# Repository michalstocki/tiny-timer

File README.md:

# Minutnik na ATtiny13A

Firmware w czystym C (`avr-gcc -Os`, bez Arduino core), instrukcja montażu na płytce stykowej, programowanie przez Arduino UNO, kalibracja i testy odbiorcze. Materiały dla użytkownika są po polsku.

| Co | Gdzie |
| --- | --- |
| Instrukcja montażu (kroki, adresy otworów, rysunki, sprawdzenia) | [docs/instrukcja-montazu.md](docs/instrukcja-montazu.md) |
| Programowanie: ArduinoISP, fuse'y, wgrywanie | [docs/programowanie.md](docs/programowanie.md) |
| Kalibracja czasu (OSCCAL) | [docs/kalibracja.md](docs/kalibracja.md) |
| Testy odbiorcze (tabela do wypełnienia) | [docs/testy-odbiorcze.md](docs/testy-odbiorcze.md) |
| Diagnostyka | [docs/diagnostyka.md](docs/diagnostyka.md) |
| Plan B: ATtiny25/45/85 z ramką i dzwonkiem | [docs/plan-b.md](docs/plan-b.md) |
| Netlista i mapa pinów | [docs/schemat.md](docs/schemat.md) |
| Gotowe pliki `.hex` i raport `avr-size` | `dist/` |
| Źródła firmware i `Makefile` | `firmware/` |
| Generator rysunków/instrukcji i weryfikacja sieci | `tools/breadboard/` |
| Symulacja logiki firmware na komputerze | `tools/sim/` |

## Szybki start

```bash
cd firmware
make                                    # buduje i drukuje rozmiary (avr-gcc z PATH lub z Arduino IDE)
make sig   PORT=/dev/cu.usbmodemXXXX    # Etap 1: sygnatura 0x1e9007 (ATtiny w gnieździe programatora)
make fuses PORT=/dev/cu.usbmodemXXXX    # Etap 2
make flash PROG=test_tone PORT=...      # Etapy 3-5: test_tone, test_display, test_buttons
make flash PROG=timer PORT=...          # Etap 6
```

Weryfikacja bez sprzętu:

```bash
tools/sim/run.sh                                 # logika minutnika (ATtiny13A)
SIM_FLAGS="-DFEATURE_BAR=1 -DFEATURE_BELL=1" tools/sim/run.sh   # plan B
SIM_TARGET=calib tools/sim/run.sh                # program kalibracyjny
cd tools/breadboard && python3 design.py && python3 test_design.py
```

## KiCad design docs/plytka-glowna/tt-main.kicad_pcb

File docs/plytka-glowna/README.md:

# Płytka główna (klin 4): projekt do zamówienia

Dwuwarstwowa płytka **40 × 24 mm** z elementami THT dla obudowy [klin 4](../obudowa-klin-4/README.md). Rozmieszczenie, zarys, otwory M2,5 i wysokości są z [`pcb-klin3`](../pcb-klin3/README.md) i **nie zostały zmienione**, więc model obudowy pozostaje ważny. Nowe jest trasowanie, stopki produkcyjne, opisy i pliki do fabryki.

**Status: Gerbery wyeksportowane i sprawdzone w KiCadzie 10.0.7** (DRC KiCada bez błędów, także z regułą odstępu 0,25 mm; Gerbery obejrzane w GerbView). Do fabryki wysyłasz [`produkcja/tt-main-gerber.zip`](produkcja/tt-main-gerber.zip). Przed zamówieniem zmierz jeszcze wysokość C3 (ryzyko 2).

## Pliki

| Plik | Co to |
| --- | --- |
| [`tt-main.kicad_pcb`](tt-main.kicad_pcb) | projekt dla KiCada (format v7, sprawdzony w KiCadzie 10.0.7): obrys, otwory, stopki, sieci, ścieżki, opisy |
| [`trasowanie.json`](trasowanie.json) | zapisane trasowanie (źródło dla pliku KiCada) |
| [`plytka-strona-elementow.svg`](plytka-strona-elementow.svg), [`plytka-strona-lutowania.svg`](plytka-strona-lutowania.svg) | podglądy obu stron z miedzią i opisami |
| [`plan-montazu.svg`](plan-montazu.svg), [`plan-pomiarow.svg`](plan-pomiarow.svg) | rysunki do instrukcji |
| [`instrukcja-montazu.md`](instrukcja-montazu.md) | montaż krok po kroku z kontrolami |
| [`bom.csv`](bom.csv) | lista części |
| [`produkcja/tt-main-gerber.zip`](produkcja/tt-main-gerber.zip) | **plik do wysłania do fabryki**: 7 warstw Gerber, wiercenia PTH i NPTH (Excellon, mm), plik zadania `.gbrjob` |
| `produkcja/` (reszta) | wynik `export_fab.sh`: rozpakowane Gerbery (`gerber/`), raporty DRC KiCada (`drc-kicad.txt`, `drc-kicad-bledy.txt`), mapy wierceń (`mapa-wiercen/`, poza zipem), podglądy `kicad-F.svg` i `kicad-B.svg` |

## Parametry do zamówienia (typowa fabryka 2-warstwowa, np. JLCPCB lub PCBWay)

| Parametr | Wartość |
| --- | --- |
| Warstwy / materiał | 2, FR-4, 1,6 mm, miedź 1 oz (35 µm) |
| Wymiary | 40 × 24 mm, narożniki R3, tolerancja zarysu ±0,2 mm (obudowa przyjmuje ±0,3) |
| Wykończenie pól | HASL bezołowiowy (do lutowania ręcznego wystarczy; ENIG droższy, bez zalet tutaj) |
| Maska, opis | domyślna zielona maska i biały opis |
| Najmniejsza ścieżka / odstęp | 0,30 / 0,28 mm w projekcie (fabryki dają 0,127 mm, więc duży zapas) |
| Najmniejsze wiercenie | 0,4 mm (przelotka, 1 szt.), pola 0,8…1,2 mm, otwór M2,5: 2,7 mm niemetalizowany |
| Liczba sztuk | najmniejsza oferowana (zwykle 5); wystarczy do próby i zapasu |
| Pozostałe opcje | domyślne; fabryka może dodać numer zamówienia na płytce (w miejscu bez miedzi), na ogół można go wyłączyć za dopłatą |

Nazwy opcji w formularzach fabryk różnią się, ale wszystkie powyższe wartości są standardowe. **Zamów kilka sztuk**: płytka jest mała i tania, a pierwsza wersja zawsze może wymagać poprawki.

## Co sprawdziłem

- **DRC własny** ([`tools/pcb/fab_drc.py`](../../tools/pcb/fab_drc.py)), na dokładnej geometrii: 0 błędów. Najmniejszy odstęp miedzi **0,28 mm** (wymagane 0,25), miedź ≥ 0,5 mm od krawędzi płytki, miedź ≥ 3,0 mm od osi otworów M2,5, pierścienie pól ≥ 0,4 mm, przelotka 0,8/0,4 (pierścień 0,2 mm), odstęp otworów ≥ 1,18 mm. Test ujemny: usunięta ścieżka, ścieżka w polu innej sieci i miedź przy krawędzi są wykrywane.
- **Łączność (LVS):** z geometrii miedzi wyliczona łączność jest zgodna z netlistą: każda z 12 sieci w jednym kawałku, 0 zwarć.
- **Netlista** zgodna z referencją z [`tools/breadboard/design.py`](../../tools/breadboard/design.py) (ta sama, z której powstała instrukcja na płytce stykowej), po pominięciu przycisków, modułu OLED i opcjonalnych R7/R8.
- **Zgodność z obudową:** żaden element nie został przesunięty, obrysy i wysokości są z `board.py`, więc wynik kolizji z [README klina 4](../obudowa-klin-4/README.md) pozostaje ważny. Zmienił się tylko rozstaw nóżek C3 (patrz niżej), w obrysie elementu.

- **KiCad 10.0.7** (`export_fab.sh`): plik wczytuje się bez błędów; DRC KiCada: 0 błędów, 0 niepołączonych pól. Zostały same dopuszczalne ostrzeżenia: 18 × brak biblioteki `TT` (stopki są wbudowane w plik), 32 × obrys elementu na polu (maska go przytnie), 4 × stykające się obrysy C2 i C3. Dodatkowo DRC z ostrzejszymi regułami (odstęp 0,25 mm, miedź–krawędź 0,5 mm, otwór–otwór 0,5 mm): 0 błędów; test ujemny z odstępem 0,29 mm wskazuje dwa miejsca z 0,28 mm przy U1.5, czyli KiCad liczy to samo co własny DRC.
- **Napisy w miedzi** (na prośbę fabryki, do kontroli, że warstwy nie są zamienione ani odbite): „TOP” na F.Cu w prawym górnym rogu strony elementów i „BOT” na B.Cu nad napisem TT-MAIN, lustrzany, więc czyta się od strony lutowania. Wysokość 1,2 mm, kreska 0,25 mm, bez sieci. Miejsce wybiera [`fab_cutext.py`](../../tools/pcb/fab_cutext.py): największy odstęp od miedzi, poza opisami i strefami otworów M2,5. DRC KiCada nie zgłasza ich nawet przy odstępie 0,4 mm; na renderze obu stron czytają się prosto.
- **Gerbery** obejrzane w GerbView (wszystkie warstwy razem) i sprawdzone w plikach: obrys 40 × 24 mm z R3, 43 pola, 1 przelotka i napis (TOP/BOT) na obu warstwach miedzi, 45 otworów w masce na każdej stronie (43 pola + 2 otwory M2,5; przelotka pod maską), opis B odbity poprawnie, wiercenia PTH Ø0,4 (przelotka), Ø0,8, Ø0,9, Ø1,2 i osobny plik NPTH z 2 × Ø2,7.
- **Poprawka po pierwszym eksporcie:** napis „TT-MAIN v1.0” wychodził 0,4 mm poza narożnik płytki, bo generator opisów zakładał zbyt wąską czcionkę (0,62 zamiast zmierzonych 0,83 wysokości na znak) i nie sprawdzał łuków narożników. Po poprawce w [`fab_silk.py`](../../tools/pcb/fab_silk.py) opisy przesunęły się o ułamki milimetra (napis DISP na stronie lutowania jest teraz pod polami), żaden nie zniknął; elementy, pola i ścieżki bez zmian.

## Zmiany względem projektu `pcb-klin3`

| Zmiana | Po co |
| --- | --- |
| C3 (elektrolit Ø5 mm): rozstaw nóżek 2,0 mm zamiast 2,54 mm | taki masz kondensator; nóżki leżą teraz na polach bez odginania |
| Pola przewodów (DISP, KEY, SPK, BAT) Ø2,0 mm zamiast Ø2,3 mm, otwór 1,2 mm | Ø2,3 na rozstawie 2,54 mm zostawiało 0,24 mm przerwy między polami SPK i BAT |
| Kwadratowe pola: pin 1 U1, plus C3, anoda D1, **BAT+**, KEY1 (GND), DISP1 (SDA) | rozpoznanie polaryzacji i początku grupy bez opisu |
| Nowe trasowanie (czysty router 45°, 1 przelotka, 276 mm ścieżek) | poprzednie było tylko próbą wykonalności na siatce 0,25 mm |
| Opisy: oznaczenia i obrysy elementów (strona elementów), nazwy pól i numery pinów (strona lutowania) | ułatwienie montażu i pomiarów |
| Napisy „TOP” / „BOT” w miedzi | wymaganie fabryki: kontrola strony i odbicia warstw po wytrawieniu |

## Ryzyka i rzeczy do sprawdzenia przed zamówieniem

1. **Podgląd fabryki.** Pliki sprawdziłem w KiCadzie, ale nie w podglądzie Gerberów u fabryki (wymaga wgrania na jej stronę). Po wgraniu zipa sprawdź, czy fabryka rozpoznała 2 warstwy i wymiar 40 × 24 mm i czy obrazek zgadza się z `produkcja/kicad-F.svg`.
2. **Wysokość C3.** Model obudowy zakłada **8,0 mm** (to założenie z [specyfikacji płytki](../pcb-klin3/specyfikacja-plytki.md), nie pomiar). Typowy elektrolit 100 µF/16 V Ø5 mm ma 11 mm, więc ten, który masz, może nie mieścić się pod sufitem obudowy. Zmierz go suwmiarką przed zamówieniem płytki: jeśli ma 11 mm, potrzebna jest niższa wersja (Ø5 × 7 mm, o ile dostępna) albo sprawdzenie, ile miejsca naprawdę jest nad C3 w modelu obudowy.
3. **Opisy na gęstej płytce.** Nie wszystkie opisy pól się zmieściły (np. pełna lista pinów DISP i KEY, plus BAT). Zamiast urwanych napisów jest nazwa grupy albo nic, a kolejność pinów i kwadratowe pole = pin 1 opisuje [instrukcja](instrukcja-montazu.md) i `plan-pomiarow.svg`.
4. **Grubość opisu 0,15 mm i wysokość 1,0 mm** są na dolnej granicy czytelności u tanich fabryk. Jeśli opis wyjdzie nieczytelny, nie ma to wpływu na działanie.
5. **Brak zabezpieczenia przed odwrotną polaryzacją baterii.** Tak jest w schemacie projektu: kwadratowe pole BAT+ i opis w instrukcji mają to ograniczyć.
6. Pozostałe założenia (wymiary modułu OLED, wysokości elementów, położenie koszyka) są takie jak w [README klina 4](../obudowa-klin-4/README.md).

## Regeneracja

```bash
python3 tools/pcb/fab_build.py              # DRC/LVS, plik KiCada, podglądy, BOM (używa zapisanego trasowania)
python3 tools/pcb/fab_build.py --reroute    # trasuje od nowa (1-3 min) i nadpisuje trasowanie.json
bash tools/pcb/export_fab.sh                # (komputer z KiCadem 8-10) DRC KiCada + Gerbery + wiercenia + zip
```

Moduły: [`fab.py`](../../tools/pcb/fab.py) (stopki, pola, opisy), [`fab_router.py`](../../tools/pcb/fab_router.py), [`fab_drc.py`](../../tools/pcb/fab_drc.py), [`fab_silk.py`](../../tools/pcb/fab_silk.py), [`fab_cutext.py`](../../tools/pcb/fab_cutext.py) (napisy w miedzi), [`fab_kicad.py`](../../tools/pcb/fab_kicad.py), [`fab_render.py`](../../tools/pcb/fab_render.py), [`fab_plan.py`](../../tools/pcb/fab_plan.py).

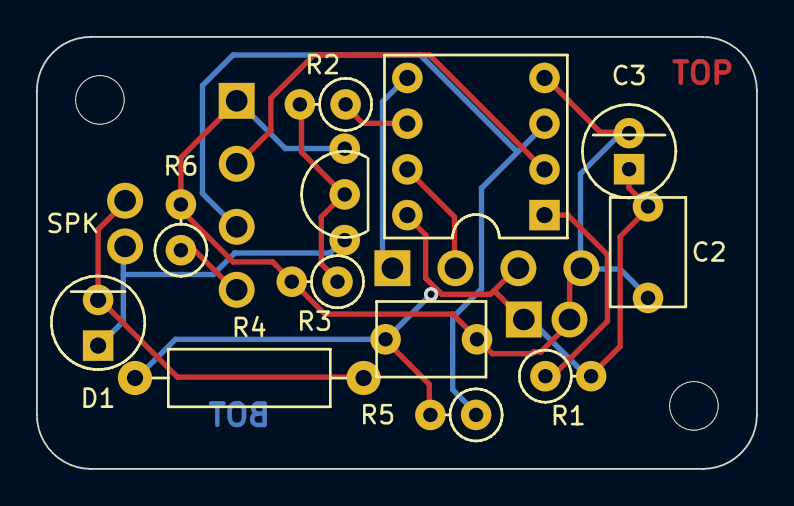
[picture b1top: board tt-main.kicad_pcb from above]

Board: 2 copper layers, 40.0 x 24.0 mm, 18 parts (0 on the bottom side), 12 nets.

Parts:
BAT: battery leads; wire2
C1, C2: 100 nF; cap5
C3: 100 uF; elco5
D1: LED; led
DISP: display module leads; wire4
KEY: button board leads; wire4
MH1, MH2: M2.5; MountingHole_M2.5
Q1: BC547B; to92
R1: 15 k; res_v
R2: 470; res_v
R3: 47 k; res_v
R4: 33, 1/2 W; res_h
R5, R6: 8.2 k; res_v
SPK: speaker leads; wire2
U1: ATtiny13A in DIP-8 socket; dip8

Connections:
BASE: Q1.B, R2.2, R3.1
COLL: D1.A, Q1.C, SPK.2
GND: BAT.2, C1.1, C2.1, C3.-, DISP.4, KEY.1, Q1.E, R3.2, R6.2, U1.4
PB1: R2.1, U1.6
PB3: KEY.2, U1.2
PB4: KEY.3, R5.1, U1.3
RESET: R1.1, U1.1
S3LOW: KEY.4, R6.1
SCL: DISP.2, U1.7
SDA: DISP.1, U1.5
SPKR: D1.K, R4.1, SPK.1
VCC: BAT.1, C1.2, C2.2, C3.+, DISP.3, R1.2, R4.2, R5.2, U1.8
